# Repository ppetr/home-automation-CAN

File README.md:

# Home automation communication network

_*Disclaimer:* This is not an officially supported Google product._

This project aims to create both SW and HW for an inexpensive home automation
communication network based on the
[CAN bus](https://en.wikipedia.org/wiki/CAN_bus) using common components and
infrastructure.

Eventually it will contain hardware plans
([KiCAD](https://en.wikipedia.org/wiki/KiCad)) and software to control
individual modules.

At the moment subdirectories contain work in progress, untested, and not
suitable for any use whatsoever.

## Design goals:

* Local with respect to network changes. That is, changing one part of the
  network should not require modification of the network as a whole.
* Easy to use. Adding or removing devices should be simple.
* Allow complex topologies, ideally multi-star.
* Use existing infrastructure - CAT 5 cables and RJ45 connectors.
* Universal - modules should be able to provide GPIO pins, as well as standard
  short-range communication buses such as I²C.
* Inexpensive.

See also
[Linearizing multi-star network for home automation](https://electronics.stackexchange.com/questions/512147/linearizing-multi-star-network-for-home-automation)
on StackExchange.

## Detailed design

### RJ45 connector for CAN

The project uses the standard [RJ45](https://en.wikipedia.org/wiki/RJ45)
connector and [CAT5](https://en.wikipedia.org/wiki/Category_5_cable) (or better
cables).

For power distribution it uses pins 4 and 5 for positive voltage and pins 7 and
8 for negative (ground) voltage. This is compatible with [Power over
Ethernet](https://en.wikipedia.org/wiki/Power_over_Ethernet). It should be
possible to use any _passive_ PoE injector up to 48V.

Pin pairs 1 & 2 and 3 & 6 are used for the CAN bus. The standard requires that
the CAN bus data connections form a serial bus. In order to support arbitrary
tree [topologies](https://en.wikipedia.org/wiki/Network_topology), each node in
the network provides a linar segment of a CAN bus. This linear segment goes
from pins 1 (_LEFT CAN+_) and 2 (_LEFT CAN-_) to pins 3 (_RIGHT CAN+_) and 6
(_RIGHT CAN-_). All these segments are then concatenated into a single serial
line.

A simple **end node** must connects pins 1-3 and 2-6 to connect the bus segment
"on its left" with the other segment "on its right". At the same time, it
connects its CAN transceiver to these pins and to the ground pins. It can also
draw power from the PoE positive voltage pins.

A **splitter node** just connects the power pins among all RJ45 connectors. The
data pin connections are more complicated: The CAN network "going from the
left" is first connected to one branch (CAN1), the "right" part of the branch
is connected to the "left" part of the other branch (CAN2), and finally
continues "to the right" (CAN3).

This corresponds to depth-first
[tree traversal](https://en.wikipedia.org/wiki/Tree_traversal) of the network.

Notice that the splitter node is fully symmetric. Therefore any connector can
be used as the one connected to the main network, and all the others as
branches. It can also split into more than two branches. However, in any case
**all branches must be connected** to nodes, even just to dummy ones that only
connect pins 1-3 and 2-6, in order to ensure that the whole network is
interconnected.

Finally, exactly one node on the network must be a **terminating node**, to
provide proper
[electrical termination](https://en.wikipedia.org/wiki/Electrical_termination).
Without such a node the whole network would form a ring and suffer from echoes
(see also [Signal reflection](https://en.wikipedia.org/wiki/Signal_reflection)).

## Contributions and future plans

Once a skeleton of the project becomes available, contributions will be
welcomed! Please see [Code of Conduct](docs/code-of-conduct.md) and
[Contributing](docs/contributing.md).

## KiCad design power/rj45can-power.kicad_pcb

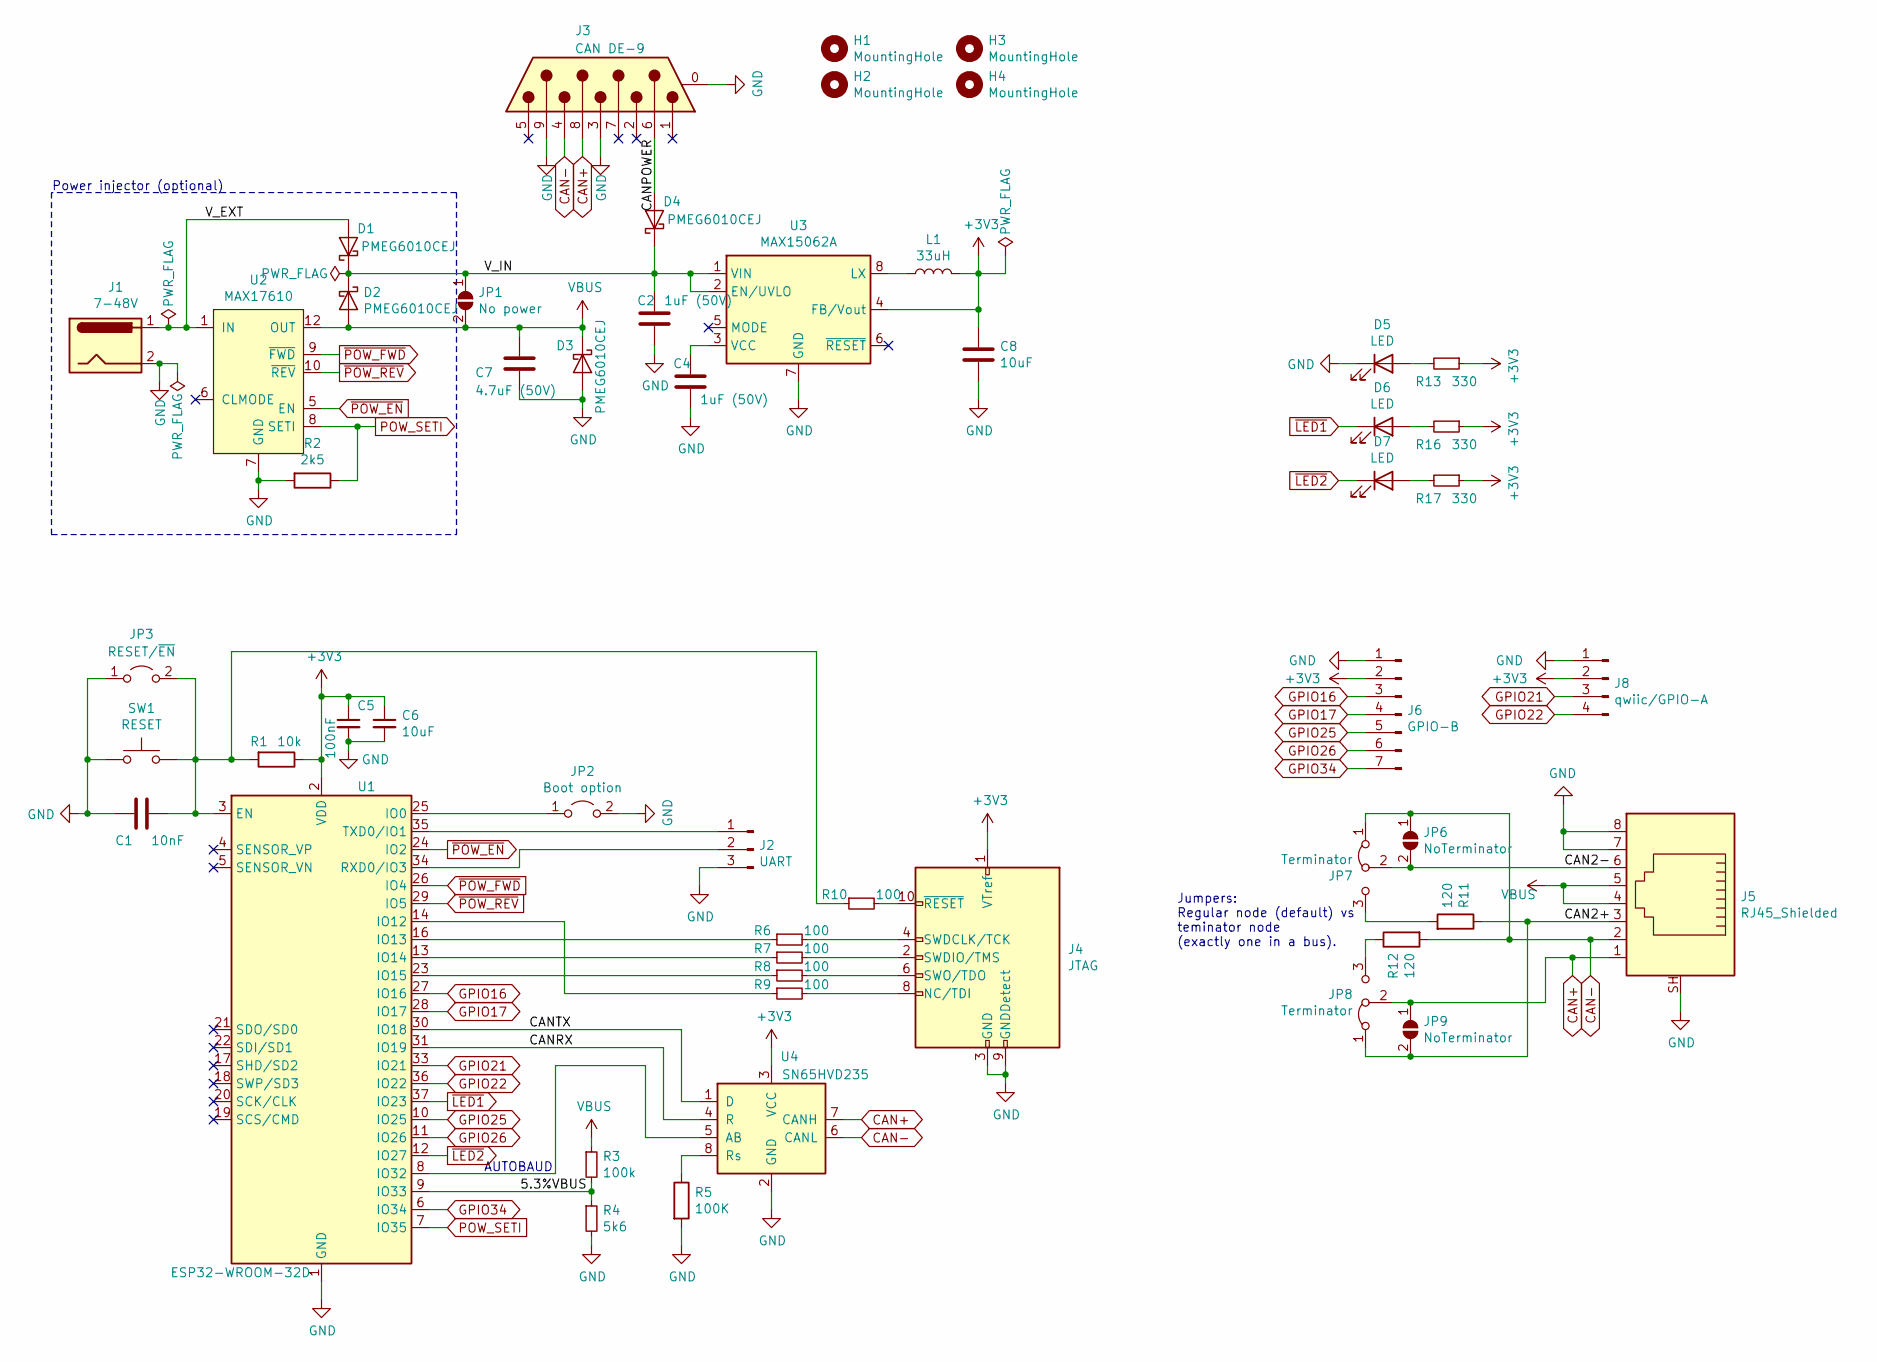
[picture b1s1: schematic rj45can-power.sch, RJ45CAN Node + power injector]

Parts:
C1: 10nF; C_0603_1608Metric_Pad1.05x0.95mm_HandSolder
C2, C4: 1uF (50V); C_0603_1608Metric_Pad1.05x0.95mm_HandSolder
C5: 100nF; C_0603_1608Metric_Pad1.05x0.95mm_HandSolder
C6, C8: 10uF; C_0603_1608Metric_Pad1.05x0.95mm_HandSolder
C7: 4.7uF (50V); C_0603_1608Metric_Pad1.05x0.95mm_HandSolder
D1, D2, D3, D4: PMEG6010CEJ; D_SOD-323F
D5, D6, D7: LED; LED_0603_1608Metric_Pad1.05x0.95mm_HandSolder
H1, H2, H3, H4: MountingHole; MountingHole_2.2mm_M2
J1: 7-48V; BarrelJack_Horizontal
J2: UART; JST_SH_BM03B-SRSS-TB_1x03-1MP_P1.00mm_Vertical
J3: CAN DE-9; DSUB-9_Male_Horizontal_P2.77x2.84mm_EdgePinOffset4.94mm_Hou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
J4: JTAG; IDC-Header_2x05_P2.54mm_Vertical
J5: RJ45_Shielded; RJ45_Ninigi_GE
J6: GPIO-B; JST_SH_BM07B-SRSS-TB_1x07-1MP_P1.00mm_Vertical
J8: qwiic/GPIO-A; JST_SH_BM04B-SRSS-TB_1x04-1MP_P1.00mm_Vertical
JP1: No power; SolderJumper-2_P1.3mm_Open_TrianglePad1.0x1.5mm
JP2: Boot option; TestPoint_2Pads_Pitch2.54mm_Drill0.8mm
JP3: RESET/~EN; PinHeader_1x02_P2.54mm_Vertical
JP6, JP9: NoTerminator; SolderJumper-2_P1.3mm_Open_Pad1.0x1.5mm
JP7, JP8: Terminator; PinHeader_1x03_P2.54mm_Vertical
L1: 33uH; L_Coilcraft_LPS4018
R1: 10k; R_0603_1608Metric_Pad1.05x0.95mm_HandSolder
R2: 2k5; R_0603_1608Metric_Pad1.05x0.95mm_HandSolder
R3: 100k; R_0603_1608Metric_Pad1.05x0.95mm_HandSolder
R4: 5k6; R_0603_1608Metric_Pad1.05x0.95mm_HandSolder
R5: 100K; R_0603_1608Metric_Pad1.05x0.95mm_HandSolder
R6, R7, R8, R9, R10: 100; R_0603_1608Metric_Pad1.05x0.95mm_HandSolder
R11, R12: 120; R_0603_1608Metric_Pad1.05x0.95mm_HandSolder
R13, R16, R17: 330; R_0603_1608Metric_Pad1.05x0.95mm_HandSolder
SW1: RESET; SW_SPST_FSMSM
U1: ESP32-WROOM-32D; ESP32-WROOM-32
U2: MAX17610
U3: MAX15062A; DFN-8_2x2mm_P0.5mm
U4: SN65HVD235; SOIC-8_3.9x4.9mm_P1.27mm

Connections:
+3V3: C5.1, C6.1, C8.1, J4.1 (VTref), J6.2, J8.2, L1.2, R1.1, R13.1, R16.1, R17.1, U1.2 (VDD), U3.4 (FB/Vout), U4.3 (VCC)
/5.3%VBUS: R3.2, R4.1, U1.9 (IO33)
/CAN2+: J5.3, JP8.1 (A), JP9.2 (B), R11.1
/CAN2-: J5.6, JP6.2 (B), JP7.2 (C)
/CANPOWER: D4.2 (A), J3.6
/CANRX: U1.31 (IO19), U4.4 (R)
/CANTX: U1.30 (IO18), U4.1 (D)
/V_EXT: D1.2 (A), J1.1, U2.1 (IN)
/V_IN: C2.1, D1.1 (K), D2.1 (K), D4.1 (K), JP1.1 (A), U3.1 (VIN), U3.2 (EN/UVLO)
CAN+: J3.8, J5.1, JP8.2 (C), JP9.1 (A), U4.7 (CANH)
CAN-: J3.4, J5.2, JP6.1 (A), JP7.1 (A), R12.2, U4.6 (CANL)
GND: C1.2, C2.2, C4.2, C5.2, C6.2, C7.1, C8.2, D3.2 (A), D5.1 (K), J1.2, J2.3, J3.0 (PAD), J3.3, J3.9, J4.3 (GND), J4.5 (GND), J4.9 (GNDDetect), J5.7, J5.8, J5.SH, J6.1, J8.1, JP2.2 (B), JP3.1 (A), R2.2, R4.2, R5.2, SW1.1, U1.1 (GND), U1.15 (GND), U1.38 (GND), U1.39 (GND), U2.7 (GND), U3.7 (GND), U4.2 (GND)
GPIO16: J6.3, U1.27 (IO16)
GPIO17: J6.4, U1.28 (IO17)
GPIO21: J8.3, U1.33 (IO21)
GPIO22: J8.4, U1.36 (IO22)
GPIO25: J6.5, U1.10 (IO25)
GPIO26: J6.6, U1.11 (IO26)
GPIO34: J6.7, U1.6 (IO34)
unnamed: C1.1, JP3.2 (B), R1.2, R10.1, SW1.2, U1.3 (EN)
unnamed: C4.1, U3.3 (VCC)
unnamed: D5.2 (A), R13.2
unnamed: D6.2 (A), R16.2
unnamed: D7.2 (A), R17.2
unnamed: J2.1, U1.35 (TXD0/IO1)
unnamed: J2.2, U1.34 (RXD0/IO3)
unnamed: J4.2 (SWDIO/TMS), R7.2
unnamed: J4.4 (SWDCLK/TCK), R6.2
unnamed: J4.6 (SWO/TDO), R8.2
unnamed: J4.8 (NC/TDI), R9.2
unnamed: J4.10 (~RESET~), R10.2
unnamed: JP2.1 (A), U1.25 (IO0)
unnamed: JP7.3 (B), R11.2
unnamed: JP8.3 (B), R12.1
unnamed: L1.1, U3.8 (LX)
unnamed: R5.1, U4.8 (Rs)
unnamed: R6.1, U1.16 (IO13)
unnamed: R7.1, U1.13 (IO14)
unnamed: R8.1, U1.23 (IO15)
unnamed: R9.1, U1.14 (IO12)
unnamed: U1.8 (IO32), U4.5 (AB)
POW_SETI: R2.1, U1.7 (IO35), U2.8 (SETI)
VBUS: C7.2, D2.2 (A), D3.1 (K), J5.4, J5.5, JP1.2 (B), R3.1, U2.12 (OUT)
~LED1: D6.1 (K), U1.37 (IO23)
~LED2: D7.1 (K), U1.12 (IO27)
~POW_EN: U1.24 (IO2), U2.5 (EN)
~POW_FWD: U1.26 (IO4), U2.9 (~FWD)
~POW_REV: U1.29 (IO5), U2.10 (~REV)

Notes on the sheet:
Power injector (optional)
AUTOBAUD
Jumpers: Regular node (default) vs teminator node (exactly one in a bus).

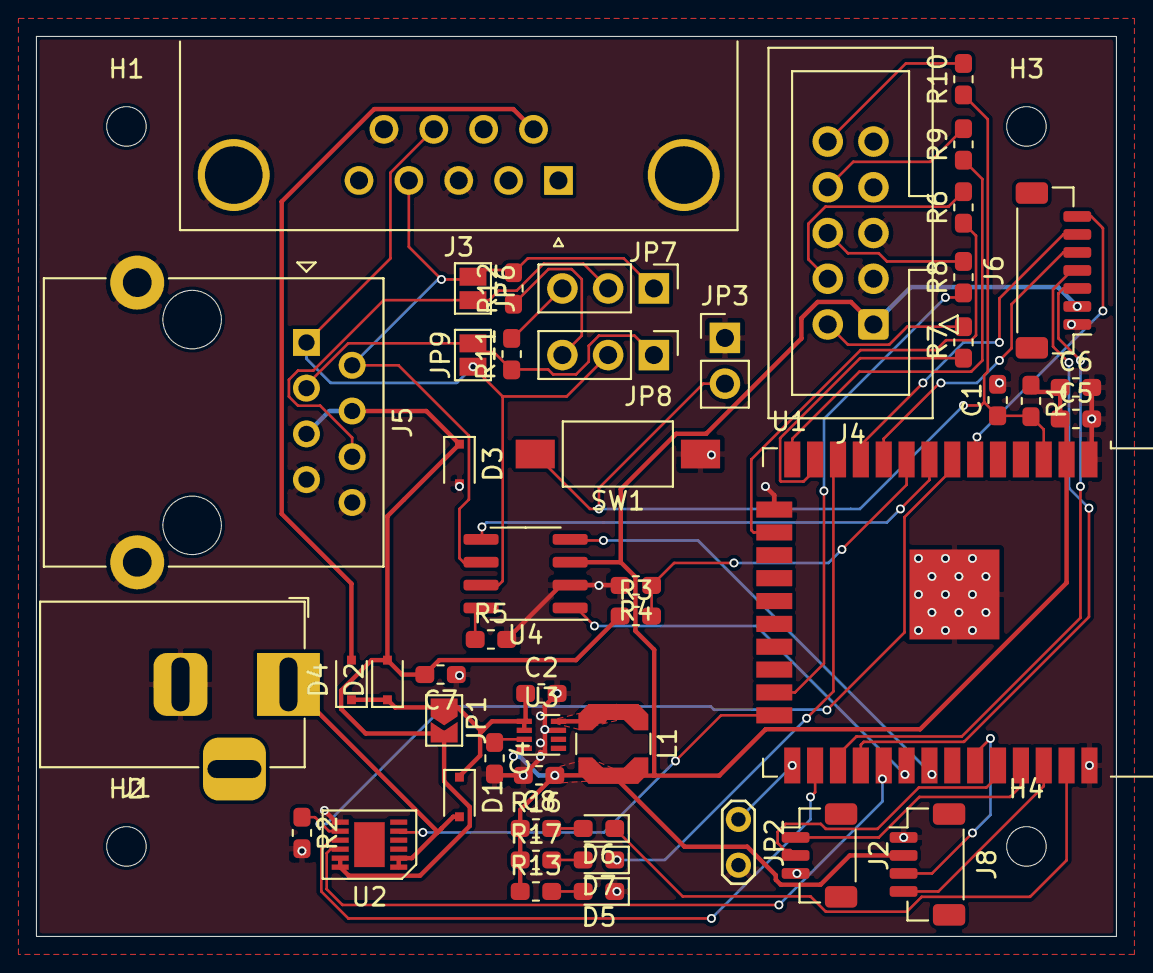
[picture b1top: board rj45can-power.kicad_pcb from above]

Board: 2 copper layers, 60.0 x 50.0 mm, 53 parts (0 on the bottom side), 48 nets.

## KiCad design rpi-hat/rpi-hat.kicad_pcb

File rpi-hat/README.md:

# Universal Raspberry Pi CAN Hat board

Provides CAN interface using the standard
[D-sub](https://en.wikipedia.org/wiki/D-subminiature) DE-9 connector and our
custom RJ-45 connector.

The board should comply to the requirements stated in
https://github.com/raspberrypi/hats. If you encounter any violation or
deviation, please open an issue.

The schema is loosely based on
https://www.disk91.com/2015/technology/hardware/design-a-raspberry-pi-hat-shield/

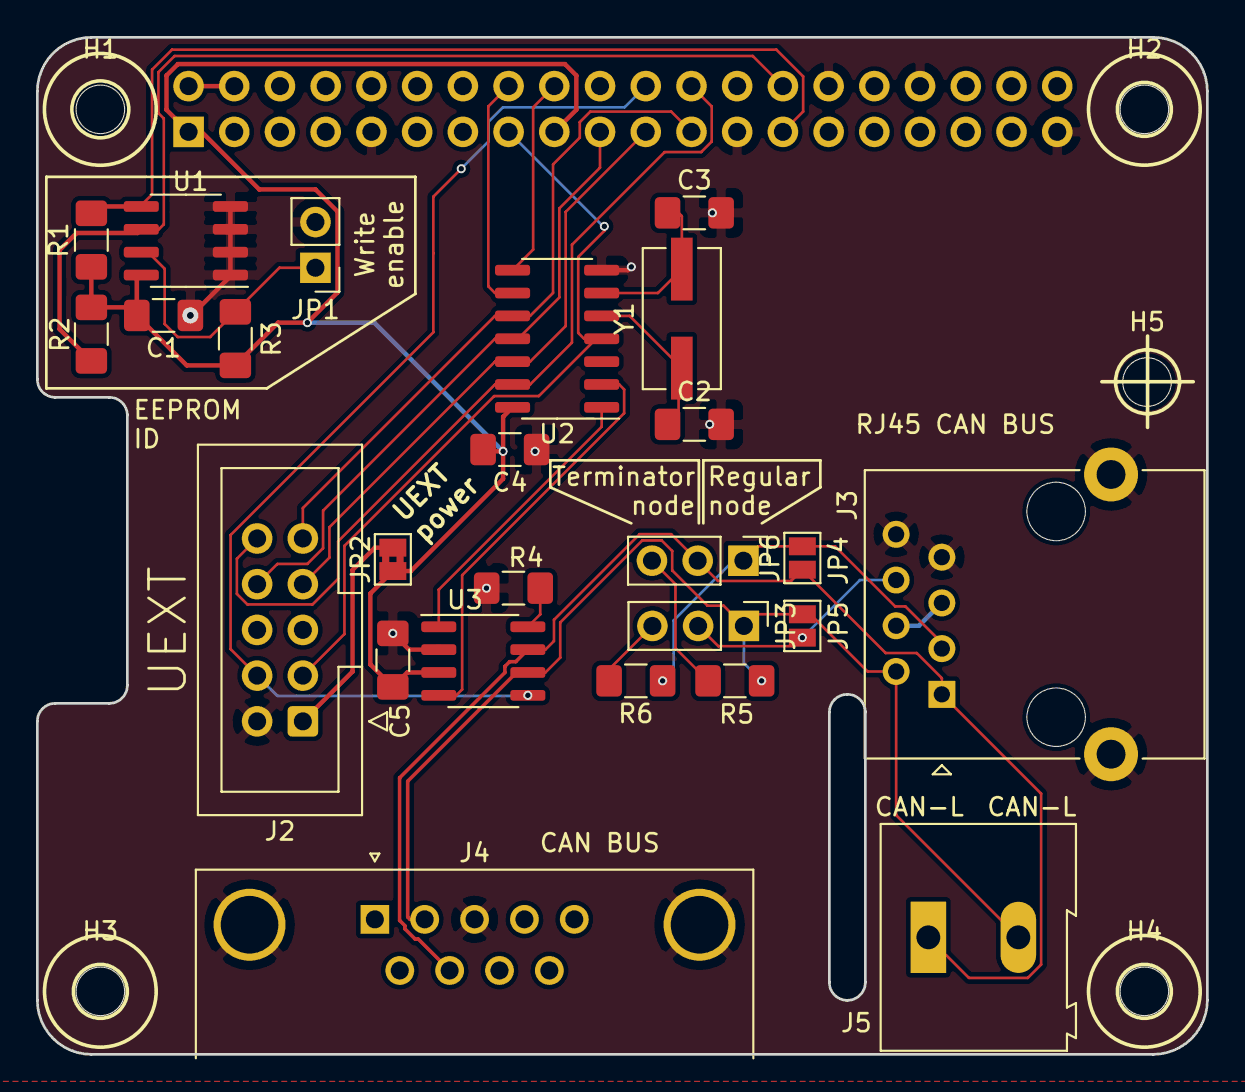
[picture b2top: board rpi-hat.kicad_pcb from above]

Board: 2 copper layers, 65.0 x 56.5 mm, 31 parts (1 on the bottom side), 27 nets.

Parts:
C1, C4, C5: 100nF; C_1206_3216Metric_Pad1.42x1.75mm_HandSolder
C2, C3: 22pF; C_1206_3216Metric_Pad1.42x1.75mm_HandSolder
H1, H2, H3, H4, H5: Drill; MountingHole_2.7mm_M2.5_DIN965
J1: Raspberry_Pi_2_3; PinSocket_2x20_P2.54mm_Vertical
J2: UEXT_Slave; IDC-Header_2x05_P2.54mm_Vertical
J3: RJ45_Shielded; RJ45_Ninigi_GE
J4: DB9 Male CAN; DSUB-9_Male_Horizontal_P2.77x2.84mm_EdgePinOffset4.94mm_Hou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
J5: Screw_Terminal_01x02; TerminalBlock_Altech_AK300-2_P5.00mm
JP1: Write Enable; PinHeader_1x02_P2.54mm_Vertical
JP2: SolderJumper_2_Bridged; SolderJumper-2_P1.3mm_Bridged2Bar_Pad1.0x1.5mm
JP3, JP4: Terminator; PinHeader_1x03_P2.54mm_Vertical
JP5, JP6: NoTerminator; SolderJumper-2_P1.3mm_Open_Pad1.0x1.5mm
R1, R2: 3k9; R_1206_3216Metric_Pad1.42x1.75mm_HandSolder
R3: 1k; R_1206_3216Metric_Pad1.42x1.75mm_HandSolder
R4: 100k; R_1206_3216Metric_Pad1.42x1.75mm_HandSolder
R5, R6: 120; R_1206_3216Metric_Pad1.42x1.75mm_HandSolder
U1: CAT24C128; SOIC-8_3.9x4.9mm_P1.27mm
U2: MCP2517FD-xSL; SOIC-14_3.9x8.7mm_P1.27mm
U3: SN65HVD235; SOIC-8_3.9x4.9mm_P1.27mm
Y1: 20MHz; Crystal_SMD_ECS_CSM3X-2Pin_7.6x4.1mm

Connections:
+3V3: C1.1, C4.2, C5.2, J1.1, J1.17, JP2.1, R1.1, R2.1, R3.1, U1.8, U2.14, U3.3
+5V: J1.2, J1.4
/CAN2+: J3.3, JP4.1, JP6.2, R6.1
/CAN2-: J3.6, JP3.2, JP5.2
/MISO: J1.21, J2.7, U2.12
/MOSI: J1.19, J2.8, U2.11
/RXCAN: U2.2, U3.4
/SCK: J1.23, J2.9, U2.10
/TXCAN: U2.1, U3.1
/UEXT_POWER: J2.1, JP2.2
/VBUS: J3.4, J3.5
/WRITE_PROTECT: JP1.1, R3.2, U1.7
/~SSEL: J1.24, J2.10, U2.13
AUTOBAUD: J1.22, J2.4, U3.5
CAN+: J3.1, J4.7, J5.1, JP4.2, JP6.1, U3.7
CAN-: J3.2, J4.2, J5.2, JP3.1, JP5.1, R5.2, U3.6
GND: C1.2, C2.2, C3.2, C4.1, C5.1, J1.6, J1.9, J1.14, J1.20, J1.25, J1.30, J1.34, J1.39, J2.2, J3.7, J3.8, J3.SH, J4.0, J4.3, JP1.2, R4.2, U1.1, U1.2, U1.3, U1.4, U2.7, U3.2
ID_SC: J1.28, R2.2, U1.6
ID_SD: J1.27, R1.2, U1.5
unnamed: C2.1, U2.5, Y1.1
unnamed: C3.1, U2.6, Y1.2
unnamed: JP3.3, R6.2
unnamed: JP4.3, R5.1
unnamed: R4.1, U3.8
~INT: J1.15, J2.3, U2.4
~INT0: J1.16, U2.9
~INT1: J1.18, U2.8

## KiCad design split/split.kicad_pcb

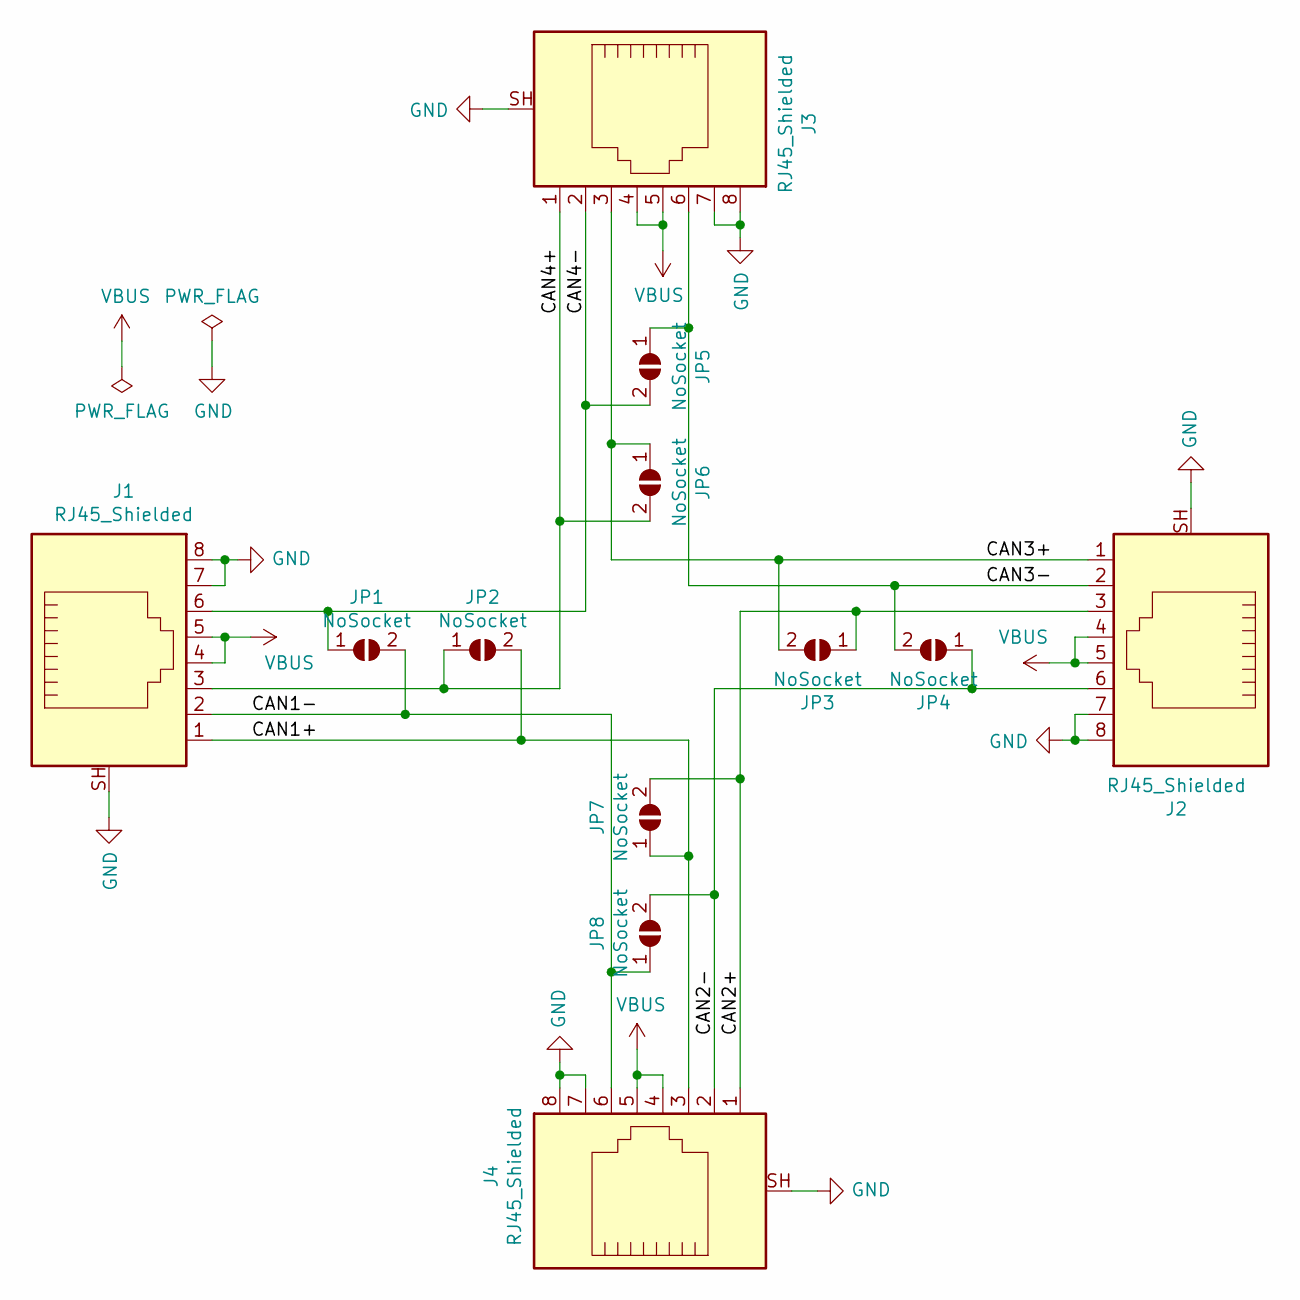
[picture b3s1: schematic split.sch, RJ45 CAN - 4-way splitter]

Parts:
J1, J2, J3, J4: RJ45_Shielded; RJ45_Ninigi_GE
JP1, JP2, JP3, JP4, JP5, JP6, JP7, JP8: NoSocket; SolderJumper-2_P1.3mm_Open_RoundedPad1.0x1.5mm

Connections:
/CAN1+: J1.1, J4.3, JP2.2 (B), JP7.1 (A)
/CAN1-: J1.2, J4.6, JP1.2 (B), JP8.1 (A)
/CAN2+: J2.3, J4.1, JP3.1 (A), JP7.2 (B)
/CAN2-: J2.6, J4.2, JP4.1 (A), JP8.2 (B)
/CAN3+: J2.1, J3.3, JP3.2 (B), JP6.1 (A)
/CAN3-: J2.2, J3.6, JP4.2 (B), JP5.1 (A)
/CAN4+: J1.3, J3.1, JP2.1 (A), JP6.2 (B)
/CAN4-: J1.6, J3.2, JP1.1 (A), JP5.2 (B)
GND: J1.7, J1.8, J1.SH, J2.7, J2.8, J2.SH, J3.7, J3.8, J3.SH, J4.7, J4.8, J4.SH
VBUS: J1.4, J1.5, J2.4, J2.5, J3.4, J3.5, J4.4, J4.5

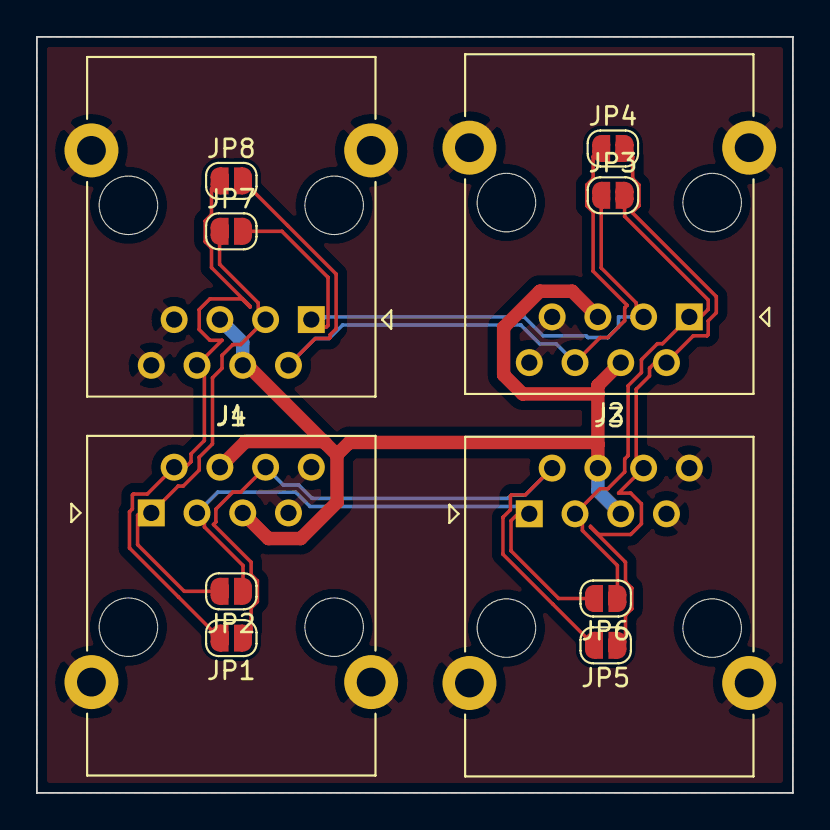
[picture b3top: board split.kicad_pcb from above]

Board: 2 copper layers, 42.0 x 42.0 mm, 12 parts (0 on the bottom side), 10 nets.

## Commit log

2020-08-28 Initial setup and README.md
2020-09-16 Initial import of KiCAD schema and PCB layout files
2020-09-17 Fix problems with project-specific library
    Use 1206/3216Metric footprints for all capacitors and resistors.
    Fix QR code to be negative and to point to the proper address.
2020-10-03 Document our connection of the CAN bus through RJ45 connectors
2020-10-07 Transparent background on rj45*.png images

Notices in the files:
power/rj45can-power.sch:
Copyright 2020 Google LLC
Licensed under the Apache License, Version 2.0
